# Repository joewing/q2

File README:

# Q2

A 16-bit discrete transistor computer with an architecture inspired
by the minicomputers of the 1960s.

## Frontpanel

The frontpanel provides the main interface to the computer.

  16 Address LEDs
  16 Data LEDs
  16 Toggle switches
  Buttons:
    - Reset/Set Address
    - Increment Address
    - Deposit
    - Start
    - Stop

## Boards

The computer is comprised of several PCBs. Other than the backplane,
all PCBs have 2x 20 pin male headers to plug into a 2-row, 40-pin
headers on the backplane.

  Name        | Quantity  | Description
  ----------- | --------- | ----------------
  Slice       | 16        | ALU/A/P/X slice
  RAM         | 1         | 16-bit RAM module
  Control     | 1         | Control module
  Clock       | 1         | Clock generator
  Backplane   | 1         | Backplane

### Clock Board

  Pin | Name        | Description
  --- | ----------- | -------------
  1   | VCC         | +5v
  2   | FAST_IN     | To fast clock switch
  3   | FAST_OUT    | To fast clock switch
  4   | START_IN    | Start switch
  5   | STOP_IN     | Stop switch
  6   | RST_IN      | Reset switch
  7   | HALT_IN     | Halt signal from control board
  8   | ~DEP_SW_IN  | Deposit switch
  9   | ~INCP_SW_IN | Increment P switch
  10  | ~RAM_CE_IO  | RAM CE bus (RAM enable)
  11  | ~RAM_WE_IO  | RAM WE bus (RAM write)
  12  | ~WRN_IO     | WRN bus (write next P)
  13  | ~WRP_IO     | WRP bus (load P from N)
  14  | WRN_OUT     | WRN signal to slice boards
  15  | WRP_OUT     | WRP signal to slice boards
  16  | RDSW_OUT    | Read switch signal to slice boards
  17  | N/C         | No connection
  18  | CLK1_OUT    | Clock phase 1
  19  | CLK2_OUT    | Clock phase 2
  20  | GND         | Ground

Note that pins 21-40 mirror 1-20.

### Control Board

  Pin | Name          | Description
  1   | VCC           | +5v
  2   | RDP_OUT       | Read P to DBUS
  3   | RDX_OUT       | Read X to ABUS
  4   | XHIN_ABUS_OUT | Read XH to ABUS

## Clock generation

A two phase, non-overlapping clock is generated using
a relaxation oscillator (CLK signal) tied to a master-slave
flip-flop.  Two NOR gates are used to generate the phases.
The output of the flip-flop is Q:

  CLK1 = ~(Q | CLK)
  CLK2 = ~(~Q | CLK)

When not running, CLK is high. At reset Q is set to 0.
This means that on reset we have CLK=1 and Q=0. Thus,
the starting sequence looks like this:

  RUN | RST | CLK | Q | C1 | C2 | Notes
  --- | --- | --- | - | -- | -- | --------------------------------
   0  |  1  |  1  | 0 |  0 |  0 | Reset button pressed
   0  |  0  |  1  | 0 |  0 |  0 | Reset button released
   1  |  0  |  0  | 0 |  1 |  0 | Run button pressed (and latched)
   1  |  0  |  1  | 1 |  0 |  0 |
   1  |  0  |  0  | 1 |  0 |  1 |
   1  |  0  |  1  | 0 |  0 |  0 |
   1  |  0  |  0  | 0 |  1 |  0 |

## Registers

  Name  | Size  | Description
  ----- | ----- | ----------------
  A     | 16    | Accumulator
  P     | 16    | Program counter
  X     | 16    | Operand
  O     | 6     | Opcode Latch (don't need to store Z)
  F     | 1     | Flag
  S     | 2     | State

## Instructions

  Instructions are 1 word.
             6 543 2 1 0
  Format is: T FFF L D Z XXXXXXXXX
  where:
    T     - type        - (0-load, 1-store)
    FFF   - function
    L     - load        - load from memory (instead of immediate)
    D     - dereference - dereference
    Z     - zero page   - use zero page for upper bits (instead of P)
    Xs    - 9-bit operand

  Instruction summary:

  Opcode  | Mnemonic  | F | Description
  ------- | --------- | - | ---------------------
  0000    | ld x      | Z | Load: A = x
  0001    | not x     | Z | NOT: A = ~x
  0010    | and x     | Z | AND: A = A & x
  0011    | or x      | Z | OR: A = A | x
  0100    | xor x     | Z | XOR: A = A ^ x
  0101    | add x     | C | Add: A = A + x
  0110    | sub x     | C | Subtract: A = A - x
  0111    | shr x     | C | Shift right: A = x >> 1
  1000    | nop       | - | No operation
  1001    | st x      | - | Store A: [x] = A
  1010    | jnf x     | - | Jump if zero/no carry (F not set)
  1011    | jf x      | - | Jump if not-zero/carry (F set)
  1100    | j x       | - | Jump: P = x
  1101    | unused    | - | Unused
  1110    | unused    | - | Unused
  1111    | halt x    | - | Wait for x

  The flag is set if carry ('C'), non-zero ('Z'),
  or left unchanged ('-').

  Address modes are indicated as follows:

    Value | ZLD | Meaning
    ----- | --- | ---------------
    #x    | 100 | immediate
    x     | 010 | current-page relative
    @x    | 011 | indirect through current page
    =x    | 110 | zero-page relative
    @=x   | 111 | indirect through zero page

  Note that store instructions do not set 'L'.

## Control Lines

  - RDP_ABUS = STATE_FETCH
  - RDX_ABUS = STATE_LOAD | STATE_DEFER | STATE_EXEC
  - WRO_DBUS = STATE_FETCH & WS
  - XHIN_ABUS = STATE_FETCH & DBUS[ZBIT]
  - XLIN_ABUS = 0
  - XHIN_DBUS = STATE_LOAD | STATE_DEREF
  - XLIN_DBUS = 1
  - WRX = (STATE_FETCH & WS)
        | (STATE_LOAD & WS & OP[LOAD_BIT])
        | (STATE_DEREF & WS & OP[DEREF_BIT])
  - WRA = WRF = STATE_EXEC & TYPE0 & WS
  - RDA_DBUS = STATE_EXEC & TYPE1 & FUNC1
  - PIN_NEXT = STATE_FETCH
  - PIN_X = STATE_EXEC
  - RDM_DBUS = ~STATE_EXEC
  - WRP = (STATE_FETCH & WS) | JUMP
        | (STATE_EXEC & TYPE1 & WS & FUNC4)
        | (STATE_EXEC & TYPE1 & WS & FUNC3 & F)
        | (STATE_EXEC & TYPE1 & WS & FUNC2 & ~F)
  - WRM_DBUS = STATE_EXEC & TYPE1 & WS & (FUNC1 | FUNC6)
  - HALT = STATE_EXEC & TYPE1 & FUNC7 & WS

## States

  - FETCH  - Fetch instruction
    - RDP_ABUS
    - RDM_DBUS
    - WRO_DBUS
    - XHIN_ABUS = DBUSL[Z_BIT]
    - XLIN_DBUS
    - WRX
    - PIN_NEXT
    - WRP
  - LOAD    - Load memory
    - RDX_ABUS
    - RDM_DBUS
    - XHIN_DBUS
    - XLIN_DBUS
    - WRX = O[LBIT]
  - DEREF   - Dereference
    - RDX_ABUS
    - RDM_DBUS
    - XHIN_DBUS
    - XLIN_DBUS
    - WRX = O[DBIT]
  - EXEC    - Execute
    - RDX_ABUS

## Examples

; Call a function
  ld    #+2   ; return pointer in A
  j     func
  ; function returns here

; Return to caller, return pointer in A
func:
  st    =ra
  ; do some stuff
  j     @=ra

; push =x onto the stack
; Return address in A.
; Assumes =x, =ra, and =sp are in the zero page.
; 7 words
push:
  st    =ra   ; save return address
  ld    =x    ; load value to save
  st    @=sp  ; save to the stack
  ld    =sp   ; load stack pointer
  sub   #1    ; decrement
  st    =sp   ; save updated stack pointer
  j     @=ra  ; return

; pop A off the stack
; Assumes =ra and =sp are in the zero page.
; 6 words
pop:
  st    =ra   ; save return address
  ld    =sp   ; load current stack pointer
  add   #1    ; increment
  st    =sp   ; save updated stack pointer
  ld    @=sp  ; load top of the stack
  j     @=ra  ; return

; Set =n bytes at =ptr to =x
; Destroys =n and =ptr
; Assumes A is the return address
; 11 words
memset:
  st    =ra   ; save return address
memset_loop:
  ld    =n    ; load current count
  jnf   @=ra  ; return if zero
  sub   #1    ; decrement
  st    =n    ; save updated count
  ld    =x    ; load value to save
  st    @=ptr ; save it
  ld    =ptr  ; increment pointer
  add   #1
  st    =ptr
  j     memset_loop

; Copy =src to =dest
; 11 words
strcpy:
  st    =ra
strcpy_loop:
  ld    @=src
  st    @=dest
  jnf   @=ra
  ld    =src
  add   #1
  st    =src
  ld    =dest
  add   #1
  st    =dest
  j     strcpy_loop

; Shift =x right =n bits
unsignedShiftRight:
  st    =ra
unsignedShiftRightLoop:
  ld    =n
  jnf   @=ra
  sub   #1
  st    =n
  shr   =x
  st    =x
  j     unsignedShiftRightLoop

; Add two 32 bit numbers, at =x and =y, result in =x (little-endian)
add32:
  st    =ra
  ld    =x
  add   =y
  st    =x
  jf    add32_carry
  ld    =x+1
  j     add32_cont
add32_carry:
  ld    =x+1
  add   #1
add32_cont:
  add   =y+1
  st    =x+1
  j     @=ra

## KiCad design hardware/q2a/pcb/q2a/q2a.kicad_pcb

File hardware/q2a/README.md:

# Q2A

Hardware for the Q2 12-bit computer made from programmable logic devices.
Compared to the original Q2, the Q2A should be easier to have fabricated
(it uses through-hole components making it easy to hand assemble). In
addition, the Q2A has a faster clock and a nicer enclosure.

Note that the current iteration of the Q2A does not support the memory
extension device or I2C.

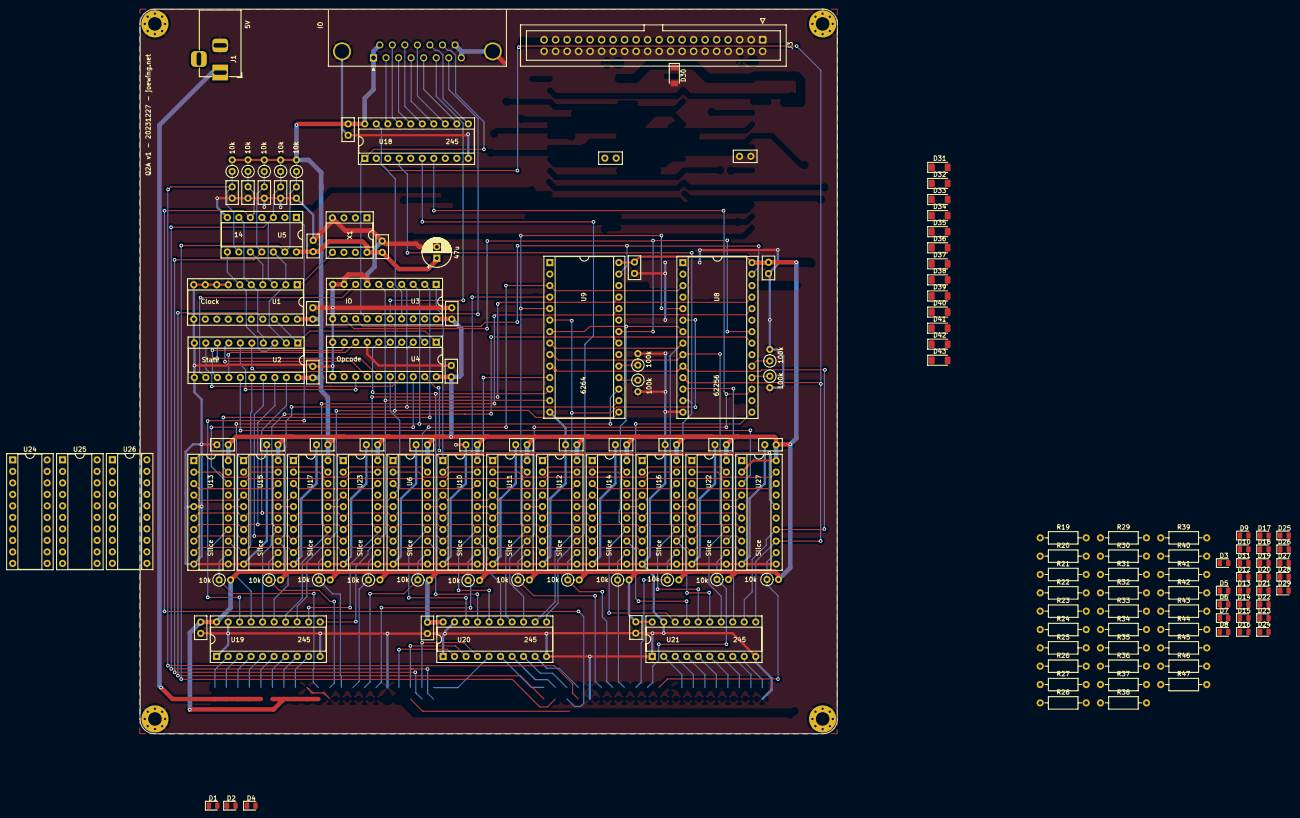
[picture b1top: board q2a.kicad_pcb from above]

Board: 2 copper layers, 154.0 x 160.0 mm, 159 parts (0 on the bottom side), 191 nets.

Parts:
C1, C2, C3, C4, C5, C6, C7, C8, C10, C11, C12, C13, C14, C15, C16, C17, C18, C19, C20, C21, C22, C23, C24, C25, C26, C27, C28, C29, C30, C31, C32: 0.1u; C_Disc_D5.0mm_W2.5mm_P2.50mm
C9: 47u; CP_Radial_D6.3mm_P2.50mm
D1, D2, D3, D4, D5, D6, D7, D8, D9, D10, D11, D12, D13, D14, D15, D16, D17, D18, D19, D20, D21, D22, D23, D24, D25, D26, D27, D28, D29: LED; LED_0805_2012Metric
D30, D31, D32, D33, D34, D35, D36, D37, D38, D39, D40, D41, D42, D43: 1N4148; D_MiniMELF
H1, H2, H3, H4: MountingHole_Pad; MountingHole_3mm_Pad_Via
J1: Barrel_Jack_MountingPin; BarrelJack_Horizontal
J2: IO; DSUB-15_Female_Horizontal_P2.77x2.84mm_EdgePinOffset7.70mm_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
J3: Programmer; IDC-Header_2x20_P2.54mm_Vertical
R1, R2, R3, R4, R5, R6, R11, R12, R13, R14, R15, R16, R17, R18, R48, R49, R50: 10k; R_Axial_DIN0207_L6.3mm_D2.5mm_P2.54mm_Vertical
R7, R8, R9, R10: 100k; R_Axial_DIN0207_L6.3mm_D2.5mm_P2.54mm_Vertical
R19, R20, R21, R22, R23, R24, R25, R26, R27, R28, R29, R30, R31, R32, R33, R34, R35, R36, R37, R38, R39, R40, R41, R42, R43, R44, R45, R46, R47: 10k; R_Axial_DIN0207_L6.3mm_D2.5mm_P10.16mm_Horizontal
U1: Clock; DIP-20_W7.62mm_Socket
U2: State; DIP-20_W7.62mm_Socket
U3: IO; DIP-20_W7.62mm_Socket
U4: Opcode; DIP-20_W7.62mm_Socket
U5: 14; DIP-14_W7.62mm_Socket
U6, U10, U11, U12, U13, U14, U15, U16, U17, U22, U23, U27: Slice; DIP-20_W7.62mm_Socket
U8: 62256; DIP-28_W15.24mm_Socket
U9: 6264; DIP-28_W15.24mm_Socket
U18, U19, U20, U21: 245; DIP-20_W7.62mm_Socket
U24: Field 2; DIP-20_W7.62mm_Socket
U25: Field 1; DIP-20_W7.62mm_Socket
U26: Field 0; DIP-20_W7.62mm_Socket
X1: CXO; DIP-8_W7.62mm_Socket

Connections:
/Bit 0/COUT: U22.3 (I3), U27.18 (IO2)
/Bit 0/IOOUT: U22.2 (I2), U27.19 (IO1)
/Bit 0/NEXTX: U22.16 (IO4), U27.5 (I5)
/Bit 1/COUT: U16.3 (I3), U22.18 (IO2)
/Bit 1/IOOUT: U16.2 (I2), U22.19 (IO1)
/Bit 1/NEXTX: U16.16 (IO4), U22.5 (I5)
/Bit 2/COUT: U14.3 (I3), U16.18 (IO2)
/Bit 2/IOOUT: U14.2 (I2), U16.19 (IO1)
/Bit 2/NEXTX: U14.16 (IO4), U16.5 (I5)
/Bit 3/COUT: U12.3 (I3), U14.18 (IO2)
/Bit 3/IOOUT: U12.2 (I2), U14.19 (IO1)
/Bit 3/NEXTX: U12.16 (IO4), U14.5 (I5)
/Bit 4/COUT: U11.3 (I3), U12.18 (IO2)
/Bit 4/IOOUT: U11.2 (I2), U12.19 (IO1)
/Bit 4/NEXTX: U11.16 (IO4), U12.5 (I5)
/Bit 5/COUT: U10.3 (I3), U11.18 (IO2)
/Bit 5/IOOUT: U10.2 (I2), U11.19 (IO1)
/Bit 5/NEXTX: U10.16 (IO4), U11.5 (I5)
/Bit 6/COUT: U6.3 (I3), U10.18 (IO2)
/Bit 6/IOOUT: U6.2 (I2), U10.19 (IO1)
/Bit 6/NEXTX: U6.16 (IO4), U10.5 (I5)
/Bit 7/COUT: U6.18 (IO2), U23.3 (I3)
/Bit 7/IOOUT: U6.19 (IO1), U23.2 (I2)
/Bit 7/NEXTX: U6.5 (I5), U23.16 (IO4)
/Bit 8/COUT: U17.3 (I3), U23.18 (IO2)
/Bit 8/IOOUT: U17.2 (I2), U23.19 (IO1)
/Bit 8/NEXTX: U17.16 (IO4), U23.5 (I5)
/Bit 10/CIN: U15.3 (I3), U17.18 (IO2)
/Bit 10/COUT: U13.3 (I3), U15.18 (IO2)
/Bit 10/IOIN: U15.2 (I2), U17.19 (IO1)
/Bit 10/IOOUT: U13.2 (I2), U15.19 (IO1)
/Bit 10/NEXTX: U13.16 (IO4), U15.5 (I5)
/Bit 10/X: U15.16 (IO4), U17.5 (I5)
ABUS0: U8.10 (A0), U9.10 (A0), U21.12 (B6), U27.14 (IO6)
ABUS1: U8.9 (A1), U9.9 (A1), U21.14 (B4), U22.14 (IO6)
ABUS2: U8.8 (A2), U9.8 (A2), U16.14 (IO6), U21.16 (B2)
ABUS3: U8.7 (A3), U9.7 (A3), U14.14 (IO6), U21.18 (B0)
ABUS4: U8.6 (A4), U9.6 (A4), U12.14 (IO6), U20.12 (B6)
ABUS5: U8.5 (A5), U9.5 (A5), U11.14 (IO6), U20.14 (B4)
ABUS6: U8.4 (A6), U9.4 (A6), U10.14 (IO6), U20.16 (B2)
ABUS7: U6.14 (IO6), U8.3 (A7), U9.3 (A7), U20.18 (B0)
ABUS8: U8.25 (A8), U9.25 (A8), U19.12 (B6), U23.14 (IO6)
ABUS9: U8.24 (A9), U9.24 (A9), U17.14 (IO6), U19.14 (B4)
ABUS10: U8.21 (A10), U9.21 (A10), U15.14 (IO6), U19.16 (B2)
ABUS11: U8.23 (A11), U9.23 (A11), U13.14 (IO6), U19.18 (B0)
C0: U2.16 (IO4), U6.9 (I9), U10.9 (I9), U11.9 (I9), U12.9 (I9), U13.9 (I9), U14.9 (I9), U15.9 (I9), U16.9 (I9), U17.9 (I9), U22.9 (I9), U23.9 (I9), U24.7 (I7), U25.7 (I7), U26.7 (I7), U27.9 (I9)
C1: U2.17 (I03), U6.8 (I8), U10.8 (I8), U11.8 (I8), U12.8 (I8), U13.8 (I8), U14.8 (I8), U15.8 (I8), U16.8 (I8), U17.8 (I8), U22.8 (I8), U23.8 (I8), U24.6 (I6), U25.6 (I6), U26.6 (I6), U27.8 (I8)
C2: U2.18 (IO2), U6.7 (I7), U10.7 (I7), U11.7 (I7), U12.7 (I7), U13.7 (I7), U14.7 (I7), U15.7 (I7), U16.7 (I7), U17.7 (I7), U22.7 (I7), U23.7 (I7), U24.5 (I5), U25.5 (I5), U26.5 (I5), U27.7 (I7)
C3: U2.19 (IO1), U6.6 (I6), U10.6 (I6), U11.6 (I6), U12.6 (I6), U13.6 (I6), U14.6 (I6), U15.6 (I6), U16.6 (I6), U17.6 (I6), U22.6 (I6), U23.6 (I6), U24.4 (I4), U25.4 (I4), U26.4 (I4), U27.6 (I6)
CARRY: U4.18 (IO2), U13.18 (IO2)
CIN0: U2.15 (IO5), U27.3 (I3)
CLK: U1.18 (IO2), U2.1 (I1/CLK), U3.1 (I1/CLK), U4.1 (I1/CLK), U6.1 (I1/CLK), U10.1 (I1/CLK), U11.1 (I1/CLK), U12.1 (I1/CLK), U13.1 (I1/CLK), U14.1 (I1/CLK), U15.1 (I1/CLK), U16.1 (I1/CLK), U17.1 (I1/CLK), U22.1 (I1/CLK), U23.1 (I1/CLK), U24.1 (I1/CLK), U25.1 (I1/CLK), U26.1 (I1/CLK), U27.1 (I1/CLK)
DBUS0: U8.11 (Q0), U18.2 (A0), U21.11 (B7), U26.3 (I3), U27.13 (IO7)
DBUS1: U8.12 (Q1), U18.3 (A1), U21.13 (B5), U22.13 (IO7), U25.3 (I3)
DBUS2: U8.13 (Q2), U16.13 (IO7), U18.4 (A2), U21.15 (B3), U24.3 (I3)
DBUS3: U8.15 (Q3), U14.13 (IO7), U18.5 (A3), U21.17 (B1)
DBUS4: U8.16 (Q4), U12.13 (IO7), U18.6 (A4), U20.11 (B7)
DBUS5: U8.17 (Q5), U11.13 (IO7), U18.7 (A5), U20.13 (B5)
DBUS6: U9.11 (Q0), U10.13 (IO7), U18.8 (A6), U20.15 (B3)
DBUS7: U4.6 (I6), U6.13 (IO7), U9.12 (Q1), U18.9 (A7), U20.17 (B1)
DBUS8: U3.6 (I6), U4.5 (I5), U9.13 (Q2), U19.11 (B7), U23.13 (IO7)
DBUS9: U3.5 (I5), U4.4 (I4), U9.15 (Q3), U17.13 (IO7), U19.13 (B5)
DBUS10: U3.4 (I4), U4.3 (I3), U9.16 (Q4), U15.13 (IO7), U19.15 (B3)
DBUS11: U3.3 (I3), U4.2 (I2), U9.17 (Q5), U13.13 (IO7), U19.17 (B1)
DEP: U1.6 (I6), U2.3 (I3), U5.8
FIELD0: R22.1, U8.2 (A12), U9.2 (A12), U26.14 (IO6)
FIELD1: R20.1, U8.26 (A13), U9.26 (A13), U25.14 (IO6)
FIELD2: R19.1, U8.1 (A14), U9.1 (A14), U24.14 (IO6)
FLAG: U2.9 (I9), U4.17 (I03)
GND: C1.2, C2.2, C3.2, C4.2, C5.2, C6.2, C7.2, C8.2, C9.2, C10.2, C11.2, C12.2, C13.2, C14.2, C15.2, C16.2, C17.2, C18.2, C19.2, C20.2, C21.2, C22.2, C23.2, C24.2, C25.2, C26.2, C27.2, C28.2, C29.2, C30.2, C31.2, C32.2, D1.1 (K), D2.1 (K), D3.1 (K), D4.1 (K), D5.1 (K), D6.1 (K), D7.1 (K), D8.1 (K), D9.1 (K), D10.1 (K), D11.1 (K), D12.1 (K), D13.1 (K), D14.1 (K), D15.1 (K), D16.1 (K), D17.1 (K), D18.1 (K), D19.1 (K), D20.1 (K), D21.1 (K), D22.1 (K), D23.1 (K), D24.1 (K), D25.1 (K), D26.1 (K), D27.1 (K), D28.1 (K), D29.1 (K), H1.1, H2.1, H3.1, H4.1, J1.2, J2.0 (PAD), J2.8, J2.15, J3.6 (GND), J3.9 (GND), J3.14 (GND), J3.20 (GND), J3.25 (GND), J3.30 (GND), J3.34 (GND), J3.39 (GND), R7.2, R8.2, R9.2, R10.2, U1.7 (I7), U1.8 (I8), U1.9 (I9), U1.10 (GND), U1.11 (I10/~OE), U2.10 (GND), U2.11 (I10/~OE), U3.7 (I7), U3.9 (I9), U3.10 (GND), U3.11 (I10/~OE), U4.7 (I7), U4.10 (GND), U4.11 (I10/~OE), U5.1, U5.7 (GND), U6.10 (GND), U6.11 (I10/~OE), U8.14 (GND), U9.14 (GND), U10.10 (GND), U10.11 (I10/~OE), U11.10 (GND), U11.11 (I10/~OE), U12.10 (GND), U12.11 (I10/~OE), U13.5 (I5), U13.10 (GND), U13.11 (I10/~OE), U14.10 (GND), U14.11 (I10/~OE), U15.10 (GND), U15.11 (I10/~OE), U16.10 (GND), U16.11 (I10/~OE), U17.10 (GND), U17.11 (I10/~OE), U18.10 (GND), U19.1 (A->B), U19.10 (GND), U19.19 (CE), U20.1 (A->B), U20.10 (GND), U20.19 (CE), U21.1 (A->B), U21.10 (GND), U21.19 (CE), U22.10 (GND), U22.11 (I10/~OE), U23.10 (GND), U23.11 (I10/~OE), U24.10 (GND), U24.11 (I10/~OE), U25.10 (GND), U25.11 (I10/~OE), U26.10 (GND), U26.11 (I10/~OE), U27.10 (GND), U27.11 (I10/~OE), X1.4 (GND)
INCP: U1.5 (I5), U2.4 (I4), U5.6
IO: U3.2 (I2), U13.19 (IO1)
unnamed: D1.2 (A), R19.2
unnamed: D2.2 (A), R20.2
unnamed: D3.2 (A), R21.2
unnamed: D4.2 (A), R22.2
unnamed: D5.2 (A), R23.2
unnamed: D6.2 (A), R24.2
unnamed: D7.2 (A), R25.2
unnamed: D8.2 (A), R26.2
unnamed: D9.2 (A), R27.2
unnamed: D10.2 (A), R28.2
unnamed: D11.2 (A), R29.2
unnamed: D12.2 (A), R30.2
unnamed: D13.2 (A), R31.2
unnamed: D14.2 (A), R32.2
unnamed: D15.2 (A), R33.2
unnamed: D16.2 (A), R34.2
unnamed: D17.2 (A), R35.2
unnamed: D18.2 (A), R36.2
unnamed: D19.2 (A), R37.2
unnamed: D20.2 (A), R38.2
unnamed: D21.2 (A), R39.2
unnamed: D22.2 (A), R40.2
unnamed: D23.2 (A), R41.2
unnamed: D24.2 (A), R42.2
unnamed: D25.2 (A), R43.2
unnamed: D26.2 (A), R44.2
unnamed: D27.2 (A), R45.2
unnamed: D28.2 (A), R46.2
unnamed: D29.2 (A), R47.2
unnamed: D30.1 (K), J3.15 (GPIO22)
unnamed: D31.1 (K), J3.12 (GPIO18/PWM0)
unnamed: D32.1 (K), J3.16 (GPIO23)
unnamed: D33.1 (K), J3.11 (GPIO17)
unnamed: D34.1 (K), J3.18 (GPIO24)
unnamed: D35.1 (K), J3.10 (GPIO15/RXD)
unnamed: D36.1 (K), J3.22 (GPIO25)
unnamed: D37.1 (K), J3.8 (GPIO14/TXD)
unnamed: D38.1 (K), J3.7 (GCLK0/GPIO4)
unnamed: D39.1 (K), J3.23 (SCLK0/GPIO11)
unnamed: D40.1 (K), J3.26 (~CE1/GPIO7)
unnamed: D41.1 (K), J3.19 (MOSI0/GPIO10)
unnamed: D42.1 (K), J3.24 (~CE0/GPIO8)
unnamed: D43.1 (K), J3.21 (MISO0/GPIO9)
unnamed: J2.10, U18.17 (B1)
unnamed: J2.12, U18.13 (B5)
unnamed: J2.13, U18.11 (B7)
unnamed: J2.11 (P111), U18.15 (B3)
unnamed: U1.1 (I1/CLK), X1.5 (OUT)
unnamed: U8.20 (~CS), U9.20 (~CS)
unnamed: R7.1, U8.18 (Q6)
unnamed: R8.1, U8.19 (Q7)
unnamed: R9.1, U9.18 (Q6)
unnamed: R10.1, U9.19 (Q7)
unnamed: J2.2, U18.18 (B0)
unnamed: J2.3, U18.16 (B2)
unnamed: J2.4, U18.14 (B4)
unnamed: J2.5, U18.12 (B6)
unnamed: R23.1, U19.2 (A0)
unnamed: R24.1, U19.3 (A1)
unnamed: R25.1, U19.4 (A2)
unnamed: R26.1, U19.5 (A3)
unnamed: R27.1, U19.6 (A4)
unnamed: R28.1, U19.7 (A5)
unnamed: R29.1, U19.8 (A6)
unnamed: R30.1, U19.9 (A7)
unnamed: R31.1, U20.2 (A0)
unnamed: R32.1, U20.3 (A1)
unnamed: R34.1, U20.4 (A2)
unnamed: R35.1, U20.5 (A3)
unnamed: R36.1, U20.6 (A4)
unnamed: R37.1, U20.7 (A5)
unnamed: R38.1, U20.8 (A6)
unnamed: R39.1, U20.9 (A7)
unnamed: R40.1, U21.2 (A0)
unnamed: R41.1, U21.3 (A1)
unnamed: R42.1, U21.4 (A2)
unnamed: R43.1, U21.5 (A3)
unnamed: R44.1, U21.6 (A4)
unnamed: R45.1, U21.7 (A5)
unnamed: R46.1, U21.8 (A6)
unnamed: R47.1, U21.9 (A7)
OP0: U2.8 (I8), U4.15 (IO5), U24.9 (I9), U25.9 (I9), U26.9 (I9)
OP1: U2.7 (I7), U4.14 (IO6)
OP2: U2.6 (I6), U4.13 (IO7)
OP3: U2.5 (I5), U4.12 (IO8)
RST: U1.2 (I2), U2.2 (I2), U5.12
RUN: R33.1, U1.17 (I03)
S0: U2.13 (IO7), U4.9 (I9)
S1: U2.14 (IO6), U4.8 (I8), U24.8 (I8), U25.8 (I8), U26.8 (I8)
START: U1.4 (I4), U5.10
STOP: U1.3 (I3), U5.4
STORE: U2.12 (IO8), U3.8 (I8)
VCC: C4.1, C7.1, C8.1, C9.1, C10.1, C11.1, C12.1, C13.1, C14.1, C15.1, C16.1, C17.1, C18.1, C19.1, C20.1, C21.1, C22.1, C23.1, C24.1, C25.1, C26.1, C27.1, C28.1, C29.1, C30.1, C31.1, C32.1, J2.1, J2.9, R1.2, R2.2, R3.2, R4.2, R5.2, R6.2, R11.2, R12.2, R13.2, R14.2, R15.2, R16.2, R17.2, R18.2, R21.1, R48.2, R49.2, R50.2, U1.20 (VCC), U2.20 (VCC), U3.20 (VCC), U4.20 (VCC), U5.14 (VCC), U6.20 (VCC), U8.28 (VCC), U9.28 (VCC), U10.20 (VCC), U11.20 (VCC), U12.20 (VCC), U13.20 (VCC), U14.20 (VCC), U15.20 (VCC), U16.20 (VCC), U17.20 (VCC), U18.20 (VCC), U19.20 (VCC), U20.20 (VCC), U21.20 (VCC), U22.20 (VCC), U23.20 (VCC), U24.20 (VCC), U25.20 (VCC), U26.20 (VCC), U27.2 (I2), U27.20 (VCC), X1.8 (Vcc)
WRF: U3.19 (IO1), U24.2 (I2), U25.2 (I2), U26.2 (I2)
X0: U4.19 (IO1), U27.16 (IO4)
ZP: U4.16 (IO4), U6.4 (I4), U10.4 (I4), U11.4 (I4), U12.4 (I4), U13.4 (I4), U14.4 (I4), U15.4 (I4), U16.4 (I4), U17.4 (I4), U22.4 (I4), U23.4 (I4), U27.4 (I4)
~DEPSW: C3.1, D32.2 (A), R3.1, U5.9
~INCPSW: C5.1, R4.1, U5.5
~IOCMD: J2.6, U3.16 (IO4)
~IOEN0: U3.17 (I03), U18.19 (CE)
~IORD: J2.14, U3.14 (IO6), U18.1 (A->B)
~IOWR: J2.7, U3.15 (IO5)
~MEMOE: U3.12 (IO8), U8.22 (~OE), U9.22 (~OE)
~MEMWE: U3.13 (IO7), U8.27 (~WE), U9.27 (~WE)
~RSTSW: C1.1, D30.2 (A), R1.1, U5.13
~STARTSW: C6.1, R5.1, U5.11
~STOPSW: C2.1, R2.1, U5.3
~SW0: D34.2 (A), R50.1, U27.12 (IO8)
~SW1: D36.2 (A), R48.1, U22.12 (IO8)
~SW2: D38.2 (A), R17.1, U16.12 (IO8)
~SW3: D40.2 (A), R15.1, U14.12 (IO8)
~SW4: D42.2 (A), R13.1, U12.12 (IO8)
~SW5: D43.2 (A), R12.1, U11.12 (IO8)
~SW6: D41.2 (A), R11.1, U10.12 (IO8)
~SW7: D39.2 (A), R6.1, U6.12 (IO8)
~SW8: D37.2 (A), R49.1, U23.12 (IO8)
~SW9: D35.2 (A), R18.1, U17.12 (IO8)
~SW10: D33.2 (A), R16.1, U15.12 (IO8)
~SW11: D31.2 (A), R14.1, U13.12 (IO8)

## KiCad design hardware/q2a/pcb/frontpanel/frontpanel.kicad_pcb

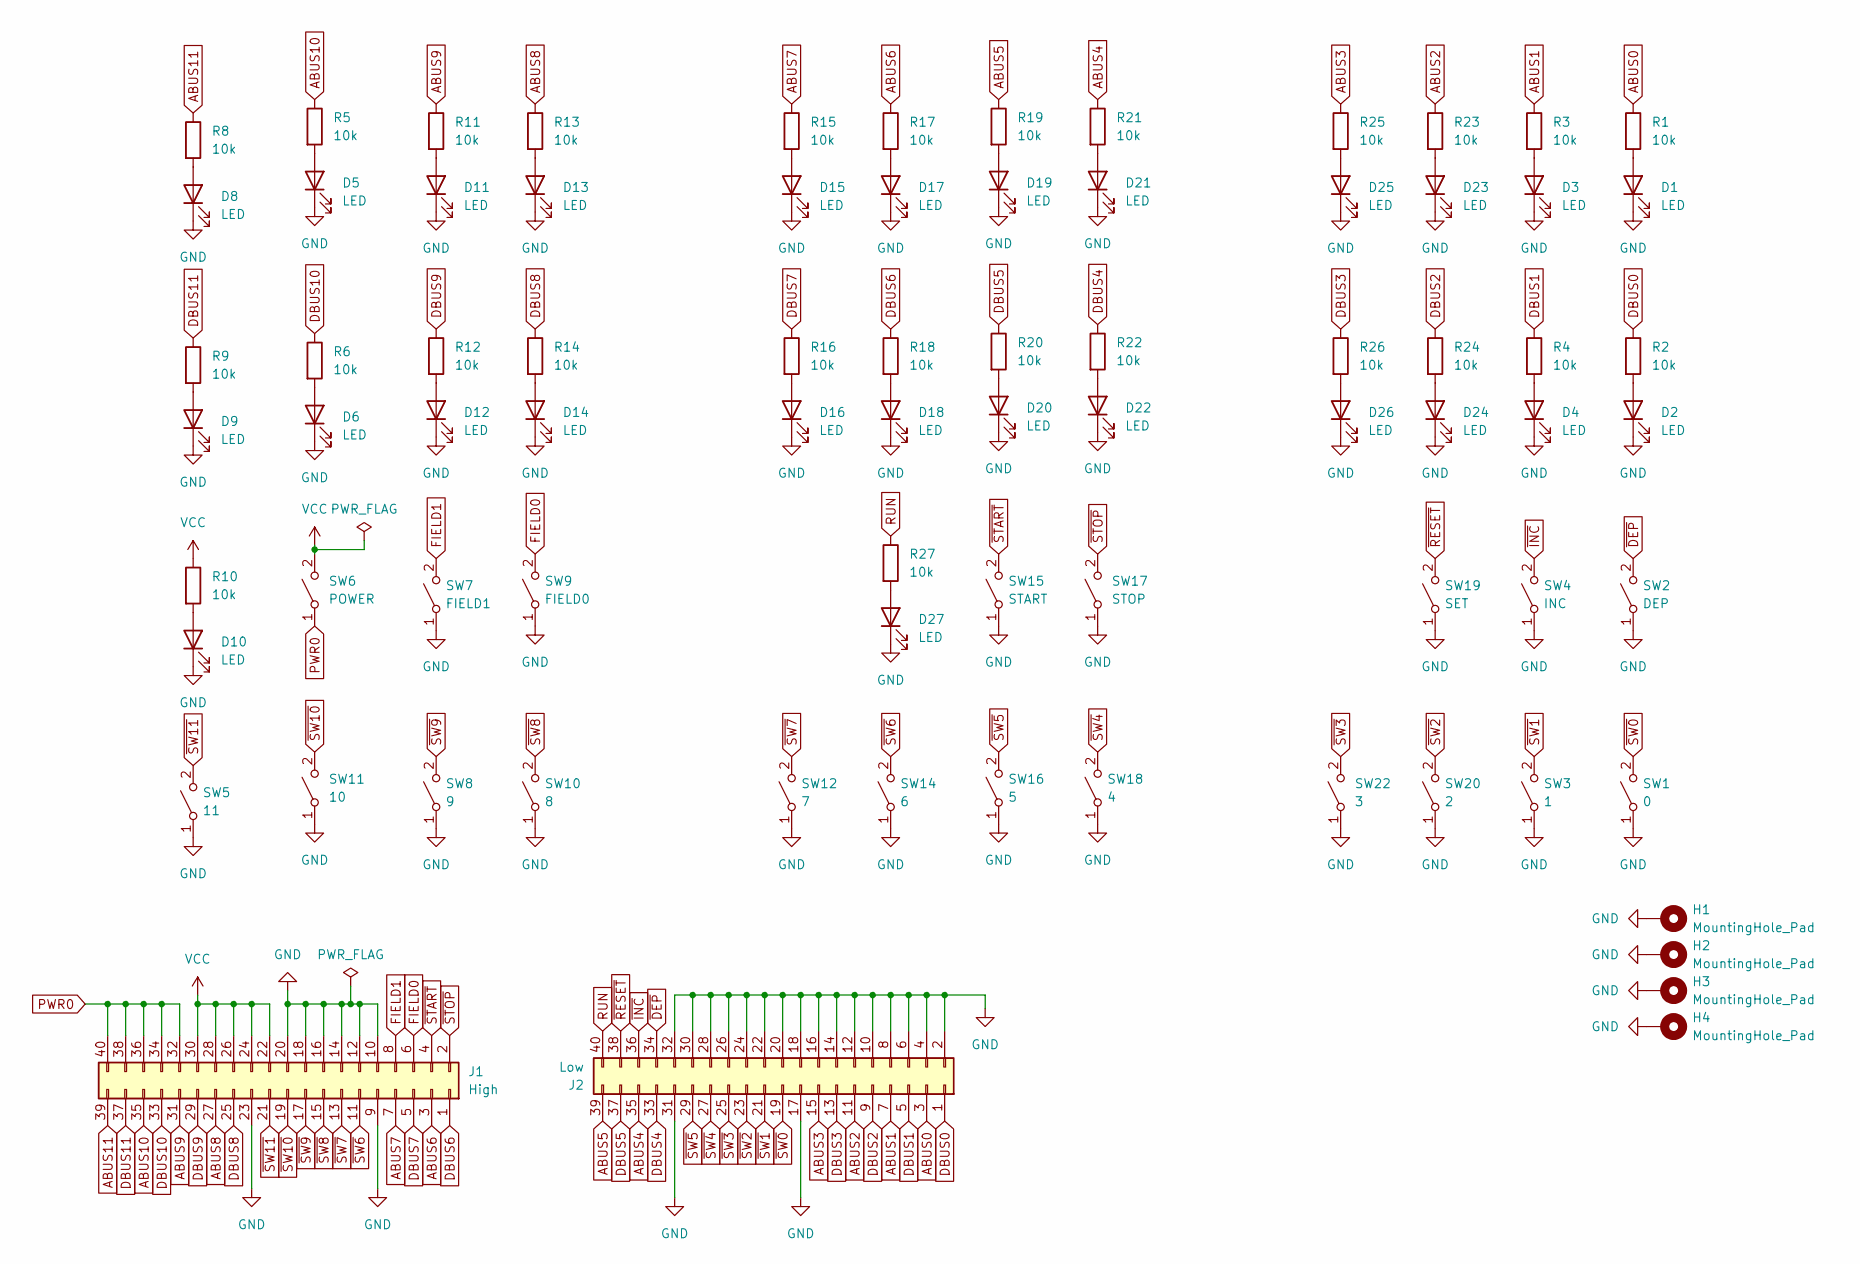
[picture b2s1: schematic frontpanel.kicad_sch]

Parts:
D1, D2, D3, D4, D5, D6, D8, D9, D10, D11, D12, D13, D14, D15, D16, D17, D18, D19, D20, D21, D22, D23, D24, D25, D26, D27: LED; LED_D3.0mm
H1, H2, H3, H4: MountingHole_Pad; MountingHole_3.2mm_M3_Pad_Via
J1: High; IDC-Header_2x20_P2.54mm_Vertical
J2: Low; IDC-Header_2x20_P2.54mm_Vertical
R1, R2, R3, R4, R5, R6, R8, R9, R10, R11, R12, R13, R14, R15, R16, R17, R18, R19, R20, R21, R22, R23, R24, R25, R26, R27: 10k; R_Axial_DIN0207_L6.3mm_D2.5mm_P10.16mm_Horizontal
SW1: 0; SW_MINI_TOGGLE
SW2: DEP; SW_MINI_TOGGLE
SW3: 1; SW_MINI_TOGGLE
SW4: INC; SW_MINI_TOGGLE
SW5: 11; SW_MINI_TOGGLE
SW6: POWER; SW_MINI_TOGGLE
SW7: FIELD1; SW_MINI_TOGGLE
SW8: 9; SW_MINI_TOGGLE
SW9: FIELD0; SW_MINI_TOGGLE
SW10: 8; SW_MINI_TOGGLE
SW11: 10; SW_MINI_TOGGLE
SW12: 7; SW_MINI_TOGGLE
SW14: 6; SW_MINI_TOGGLE
SW15: START; SW_MINI_TOGGLE
SW16: 5; SW_MINI_TOGGLE
SW17: STOP; SW_MINI_TOGGLE
SW18: 4; SW_MINI_TOGGLE
SW19: SET; SW_MINI_TOGGLE
SW20: 2; SW_MINI_TOGGLE
SW22: 3; SW_MINI_TOGGLE

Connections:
ABUS0: J2.3, R1.1
ABUS1: J2.7, R3.1
ABUS2: J2.11, R23.1
ABUS3: J2.15, R25.1
ABUS4: J2.35, R21.1
ABUS5: J2.39, R19.1
ABUS6: J1.3, R17.1
ABUS7: J1.7, R15.1
ABUS8: J1.27, R13.1
ABUS9: J1.31, R11.1
ABUS10: J1.35, R5.1
ABUS11: J1.39, R8.1
DBUS0: J2.1, R2.1
DBUS1: J2.5, R4.1
DBUS2: J2.9, R24.1
DBUS3: J2.13, R26.1
DBUS4: J2.33, R22.1
DBUS5: J2.37, R20.1
DBUS6: J1.1, R18.1
DBUS7: J1.5, R16.1
DBUS8: J1.25, R14.1
DBUS9: J1.29, R12.1
DBUS10: J1.33, R6.1
DBUS11: J1.37, R9.1
FIELD0: J1.6, SW9.2 (B)
FIELD1: J1.8, SW7.2 (B)
GND: D1.1 (K), D2.1 (K), D3.1 (K), D4.1 (K), D5.1 (K), D6.1 (K), D8.1 (K), D9.1 (K), D10.1 (K), D11.1 (K), D12.1 (K), D13.1 (K), D14.1 (K), D15.1 (K), D16.1 (K), D17.1 (K), D18.1 (K), D19.1 (K), D20.1 (K), D21.1 (K), D22.1 (K), D23.1 (K), D24.1 (K), D25.1 (K), D26.1 (K), D27.1 (K), H1.1, H2.1, H3.1, H4.1, J1.9, J1.10, J1.12, J1.14, J1.16, J1.18, J1.20, J1.23, J2.2, J2.4, J2.6, J2.8, J2.10, J2.12, J2.14, J2.16, J2.17, J2.18, J2.20, J2.22, J2.24, J2.26, J2.28, J2.30, J2.31, J2.32, SW1.1 (A), SW2.1 (A), SW3.1 (A), SW4.1 (A), SW5.1 (A), SW7.1 (A), SW8.1 (A), SW9.1 (A), SW10.1 (A), SW11.1 (A), SW12.1 (A), SW14.1 (A), SW15.1 (A), SW16.1 (A), SW17.1 (A), SW18.1 (A), SW19.1 (A), SW20.1 (A), SW22.1 (A)
unnamed: D1.2 (A), R1.2
unnamed: D2.2 (A), R2.2
unnamed: D3.2 (A), R3.2
unnamed: D4.2 (A), R4.2
unnamed: D5.2 (A), R5.2
unnamed: D6.2 (A), R6.2
unnamed: D8.2 (A), R8.2
unnamed: D9.2 (A), R9.2
unnamed: D10.2 (A), R10.2
unnamed: D11.2 (A), R11.2
unnamed: D12.2 (A), R12.2
unnamed: D13.2 (A), R13.2
unnamed: D14.2 (A), R14.2
unnamed: D15.2 (A), R15.2
unnamed: D16.2 (A), R16.2
unnamed: D17.2 (A), R17.2
unnamed: D18.2 (A), R18.2
unnamed: D19.2 (A), R19.2
unnamed: D20.2 (A), R20.2
unnamed: D21.2 (A), R21.2
unnamed: D22.2 (A), R22.2
unnamed: D23.2 (A), R23.2
unnamed: D24.2 (A), R24.2
unnamed: D25.2 (A), R25.2
unnamed: D26.2 (A), R26.2
unnamed: D27.2 (A), R27.2
PWR0: J1.32, J1.34, J1.36, J1.38, J1.40, SW6.1 (A)
RUN: J2.40, R27.1
VCC: J1.22, J1.24, J1.26, J1.28, J1.30, R10.1, SW6.2 (B)
~DEP: J2.34, SW2.2 (B)
~INC: J2.36, SW4.2 (B)
~RESET: J2.38, SW19.2 (B)
~START: J1.4, SW15.2 (B)
~STOP: J1.2, SW17.2 (B)
~SW0: J2.19, SW1.2 (B)
~SW1: J2.21, SW3.2 (B)
~SW2: J2.23, SW20.2 (B)
~SW3: J2.25, SW22.2 (B)
~SW4: J2.27, SW18.2 (B)
~SW5: J2.29, SW16.2 (B)
~SW6: J1.11, SW14.2 (B)
~SW7: J1.13, SW12.2 (B)
~SW8: J1.15, SW10.2 (B)
~SW9: J1.17, SW8.2 (B)
~SW10: J1.19, SW11.2 (B)
~SW11: J1.21, SW5.2 (B)

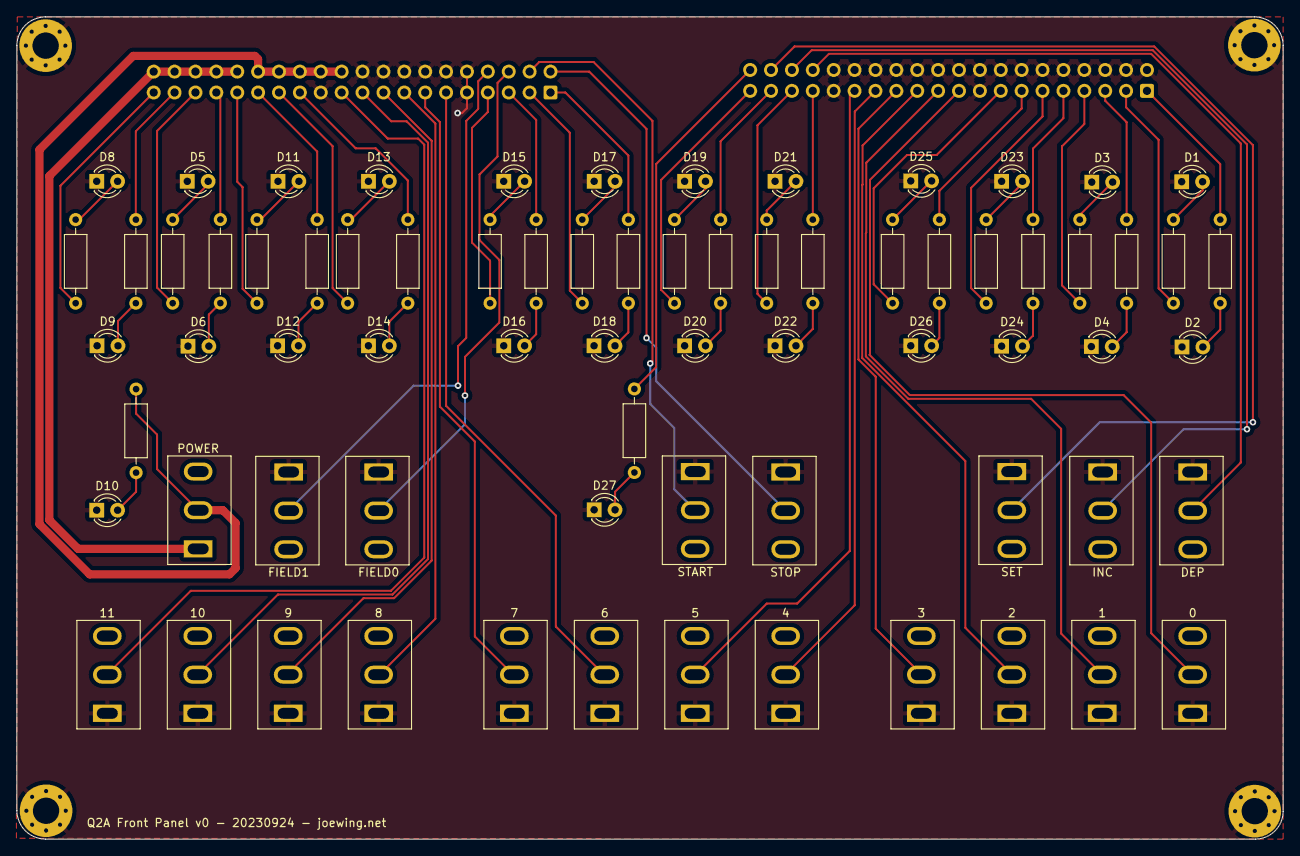
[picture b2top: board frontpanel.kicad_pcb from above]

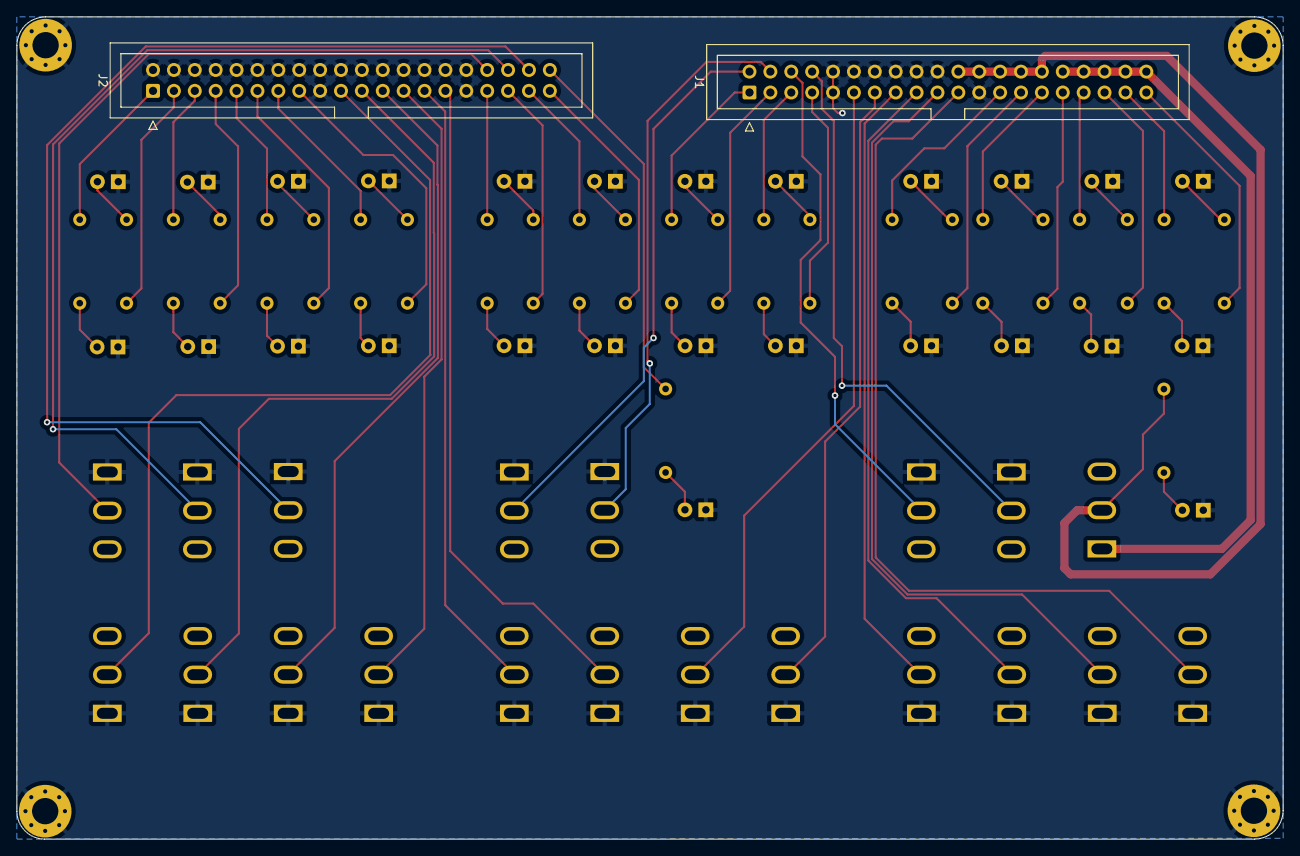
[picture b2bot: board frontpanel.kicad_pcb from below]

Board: 2 copper layers, 154.0 x 100.0 mm, 78 parts (2 on the bottom side), 73 nets.

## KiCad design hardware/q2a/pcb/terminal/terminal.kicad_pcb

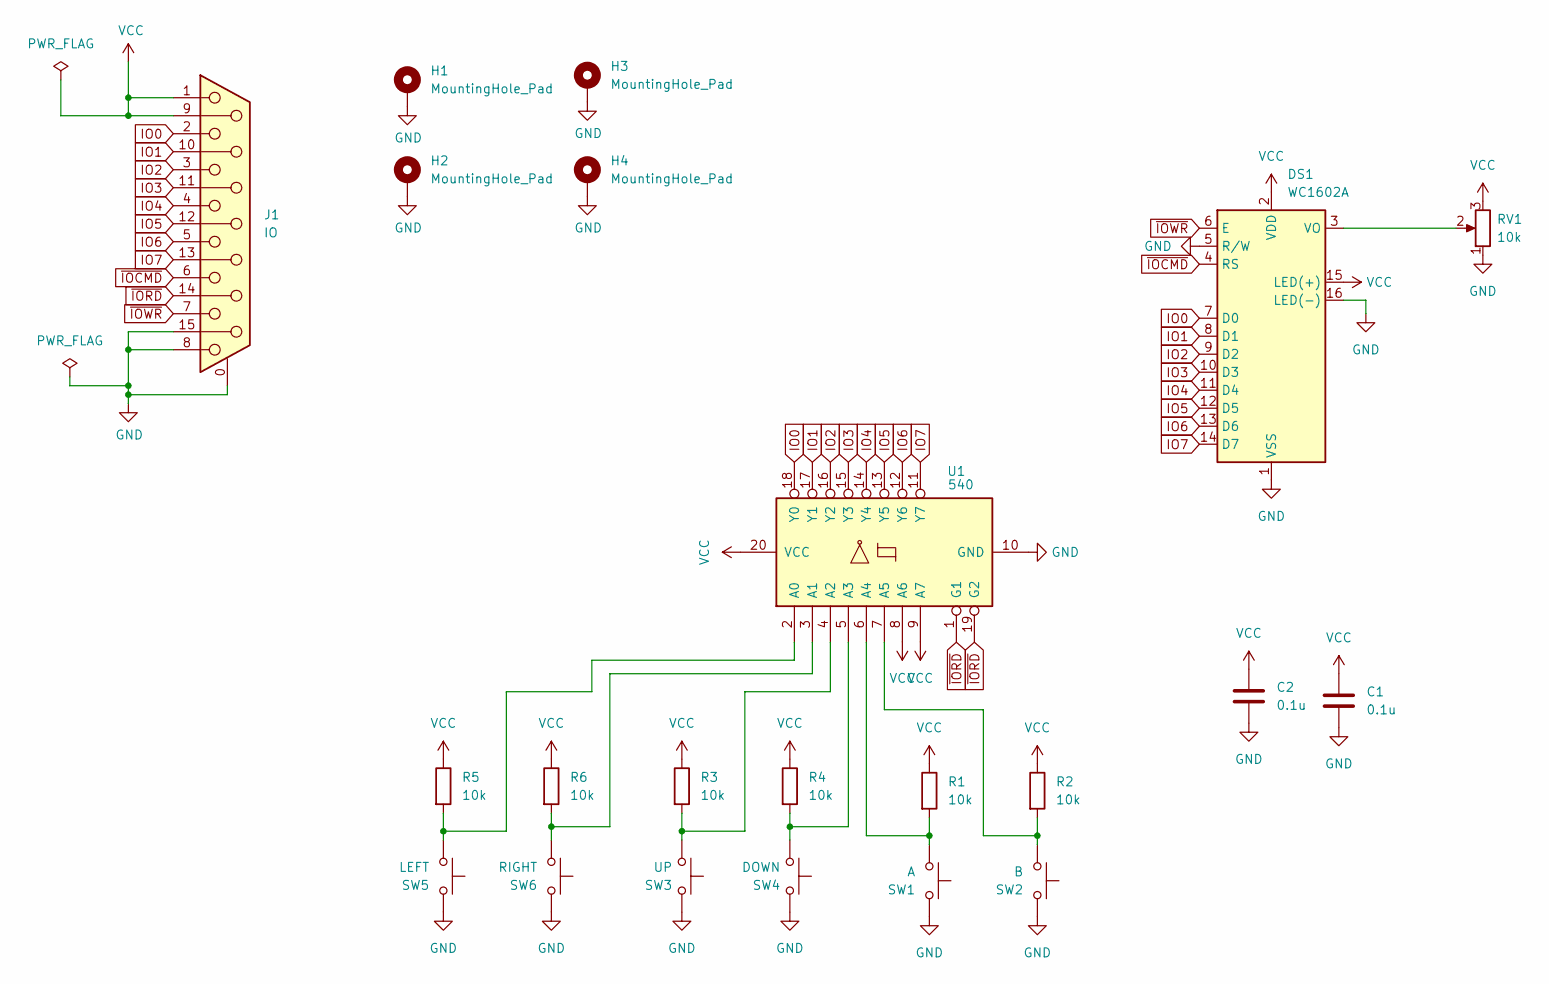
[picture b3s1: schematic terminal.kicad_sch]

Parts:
C1, C2: 0.1u; C_Disc_D3.4mm_W2.1mm_P2.50mm
DS1: WC1602A
H1, H2, H3, H4: MountingHole_Pad; MountingHole_3.2mm_M3_Pad_Via
J1: IO; DSUB-15_Female_Horizontal_P2.77x2.84mm_EdgePinOffset7.70mm_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
R1, R2, R3, R4, R5, R6: 10k; R_Axial_DIN0207_L6.3mm_D2.5mm_P10.16mm_Horizontal
RV1: 10k; Potentiometer_Bourns_3386P_Vertical
SW1: A; SW_PUSH_6mm
SW2: B; SW_PUSH_6mm
SW3: UP; SW_PUSH_6mm
SW4: DOWN; SW_PUSH_6mm
SW5: LEFT; SW_PUSH_6mm
SW6: RIGHT; SW_PUSH_6mm
U1: 540; DIP-20_W7.62mm_Socket

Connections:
GND: C1.2, C2.2, DS1.1 (VSS), DS1.5 (R/W), DS1.16 (LED(-)), H1.1, H2.1, H3.1, H4.1, J1.0 (PAD), J1.8, J1.15, RV1.1, SW1.2, SW2.2, SW3.2, SW4.2, SW5.2, SW6.2, U1.10 (GND)
IO0: DS1.7 (D0), J1.2, U1.18 (Y0)
IO1: DS1.8 (D1), J1.10, U1.17 (Y1)
IO2: DS1.9 (D2), J1.3, U1.16 (Y2)
IO3: DS1.10 (D3), J1.11 (P111), U1.15 (Y3)
IO4: DS1.11 (D4), J1.4, U1.14 (Y4)
IO5: DS1.12 (D5), J1.12, U1.13 (Y5)
IO6: DS1.13 (D6), J1.5, U1.12 (Y6)
IO7: DS1.14 (D7), J1.13, U1.11 (Y7)
unnamed: DS1.3 (VO), RV1.2
unnamed: R5.2, SW5.1, U1.2 (A0)
unnamed: R6.2, SW6.1, U1.3 (A1)
unnamed: R3.2, SW3.1, U1.4 (A2)
unnamed: R4.2, SW4.1, U1.5 (A3)
unnamed: R1.2, SW1.1, U1.6 (A4)
unnamed: R2.2, SW2.1, U1.7 (A5)
VCC: C1.1, C2.1, DS1.2 (VDD), DS1.15 (LED(+)), J1.1, J1.9, R1.1, R2.1, R3.1, R4.1, R5.1, R6.1, RV1.3, U1.8 (A6), U1.9 (A7), U1.20 (VCC)
~IOCMD: DS1.4 (RS), J1.6
~IORD: J1.14, U1.1 (G1), U1.19 (G2)
~IOWR: DS1.6 (E), J1.7

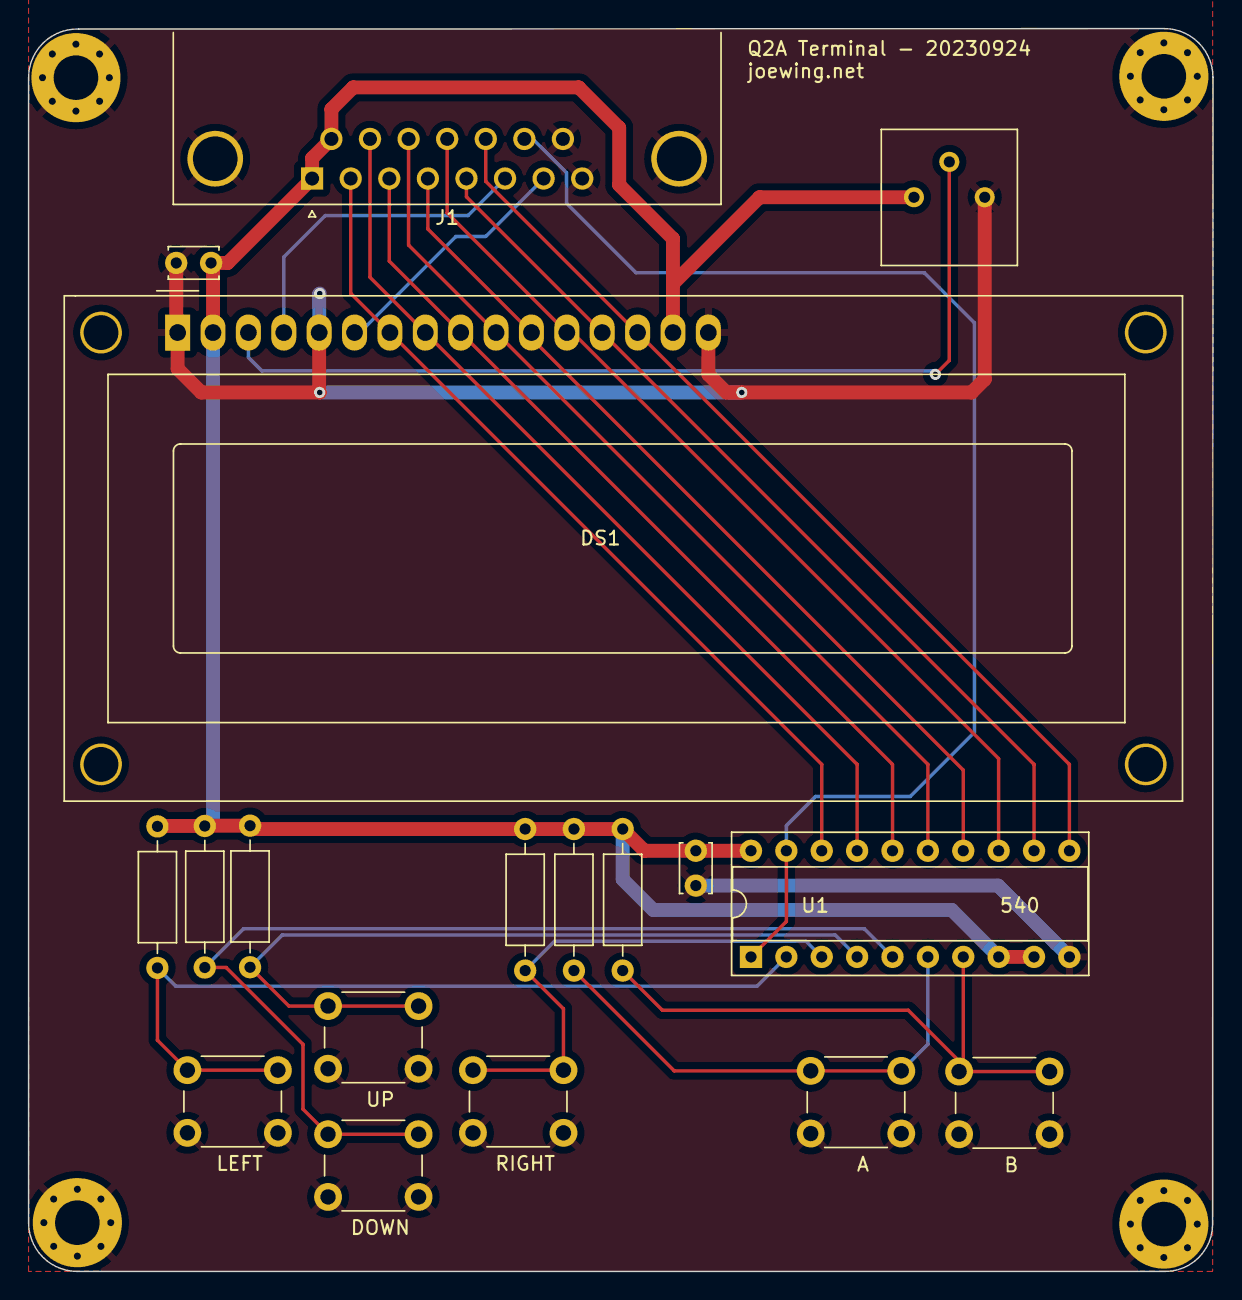
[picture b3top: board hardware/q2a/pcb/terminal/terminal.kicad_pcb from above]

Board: 2 copper layers, 85.0 x 89.2 mm, 22 parts (0 on the bottom side), 20 nets.
